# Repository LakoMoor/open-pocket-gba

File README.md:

# Open Pocket GBA

Experimental native FPGA Game Boy Advance work for the **Sipeed Tang Nano 20K (GW2AR-18)**,
based on [Open Pocket GBC](https://github.com/LakoMoor/open-pocket-gbc).
The original project history, GBC target and infrastructure are preserved.

**This is not a complete GBA implementation.** The current target executes an
original ARM/Thumb diagnostic in hardware RTL, uses SDRAM for GBA RAM/VRAM,
implements timers, ordinary four-channel DMA, keypad and LCD status/IRQ, and drives 240x160 RGB555 at 3x through the
existing 720x480 HDMI pipeline. CPU IRQ/SWI return, memory handshakes and complete
output frames have been checked in Verilator. Native CPU performance, a compatible
BIOS, full PPU, FIFO/capture DMA, audio, cartridge saves and the GBA menu are still missing.

This image is a simulated HDMI RGB capture, not a physical board demonstration.
See [confirmed progress and build results](docs/gba-progress.md),
[architecture audit](docs/gba-architecture.md), [memory/bandwidth budget](docs/gba-memory-budget.md)
and [compatibility limits](docs/gba-compatibility.md).

## Build and test

Only open-source tools: Yosys + slang, nextpnr-himbaechel, Apicula/gowin_pack,
Verilator and openFPGALoader. No mandatory Gowin EDA dependency.

```sh
python fw/gba/make_diagnostic.py
bash sim/gba/run.sh
bash sim/gba/board.sh
./build.sh gba_top
```

Override `TOOLS` to point to OSS CAD Suite; the existing Windows default is
`/e/tools/oss-cad-suite`. GBA build artifacts and timing logs go into
`build/gba_top/`. GBA timing failures prevent packing a bitstream.

The original Game Boy / Game Boy Color target remains separate:

```sh
./build.sh gbc_top
```

Its features, menu, firmware, wiring and flash instructions are documented in
[the preserved GBC README](README.gbc.md). `flash.sh` continues to select GBC;
it does not implicitly install GBA or change the existing firmware/save layout.

## Source and licensing

The console runs as FPGA logic, not software emulation on a RISC-V CPU or PC.
Only the CPU/Thumb decoder is imported from GBATang; the integration, memory
system, timer/IRQ module and diagnostic are separate work. Attribution and full
license texts are in [licenses](licenses/gba-provenance.md) and [LICENSE](LICENSE).
No proprietary BIOS or commercial ROM is included. The diagnostic's original
source and explicit instruction encodings are in `fw/gba/make_diagnostic.py`.

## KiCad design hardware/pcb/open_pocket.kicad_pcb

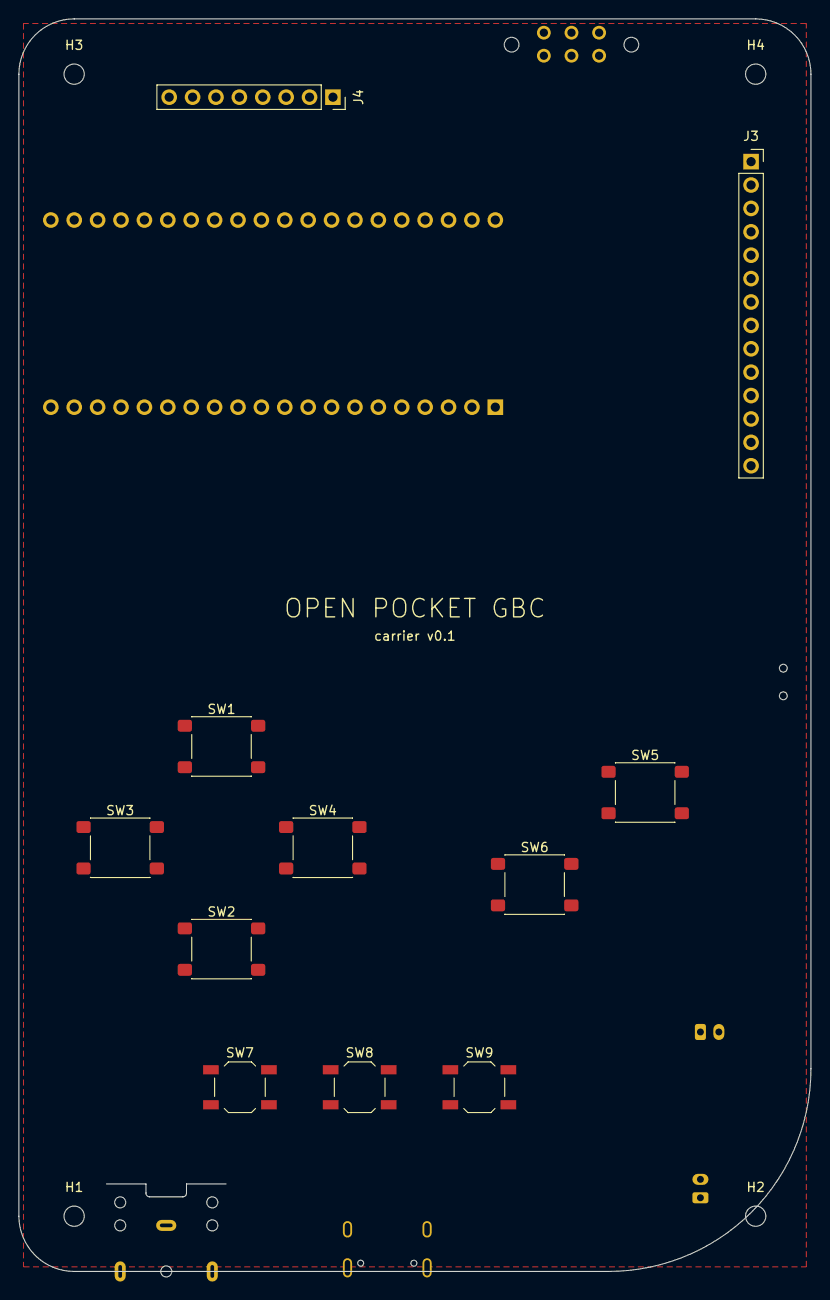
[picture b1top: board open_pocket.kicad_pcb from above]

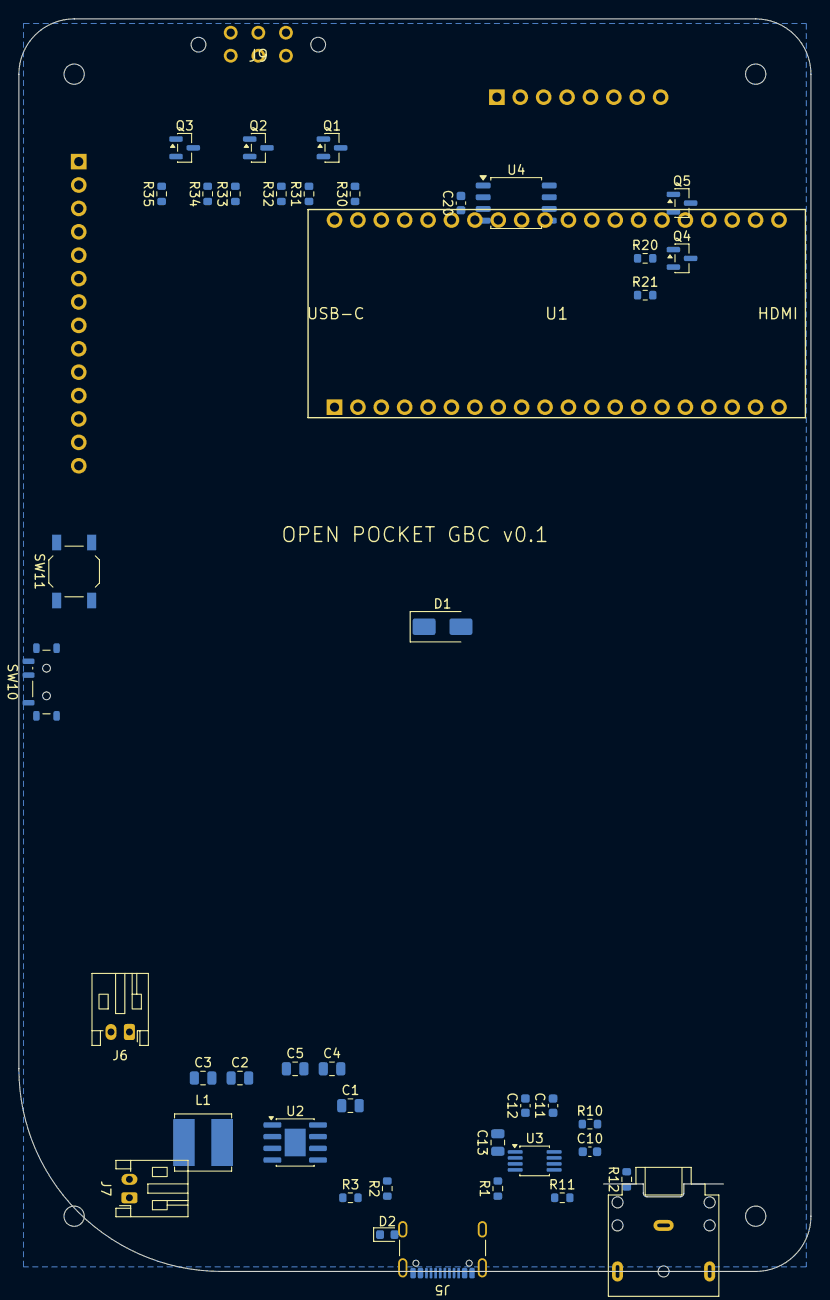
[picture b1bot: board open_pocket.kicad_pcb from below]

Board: 2 copper layers, 86.0 x 136.0 mm, 58 parts (43 on the bottom side), 48 nets, no tracks yet.

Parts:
C1, C2, C3, C13: 10uF; C_0805_2012Metric
C4, C5: 22uF; C_0805_2012Metric
C10: 10nF; C_0603_1608Metric
C11, C12: 1uF; C_0603_1608Metric
C20: 100nF; C_0603_1608Metric
D1: SS34; D_SMA
D2: LED charge; LED_0603_1608Metric
H1, H2, H3, H4: M2; MountingHole_2.2mm_M2
J3: LCD 2.4in ILI9341; PinSocket_1x14_P2.54mm_Vertical
J4: LCD 1.44in ST7735 (alt.); PinSocket_1x08_P2.54mm_Vertical
J5: USB-C (charge); USB_C_Receptacle_GCT_USB4105-xx-A_16P_TopMnt_Horizontal
J6: LiPo 3.7 V; JST_PH_S2B-PH-K_1x02_P2.00mm_Horizontal
J7: Speaker 8R 1W; JST_PH_S2B-PH-K_1x02_P2.00mm_Horizontal
J8: 3.5 mm; Jack_3.5mm_CUI_SJ1-3523N_Horizontal
J9: Link port; GB_Link_Port
L1: 1uH 4A; L_Bourns_SRN6045TA
Q1, Q2, Q3, Q4: BSS138; SOT-23
Q5: AO3401; SOT-23
R1, R2: 5.1k; R_0603_1608Metric
R3, R10: 1k; R_0603_1608Metric
R11, R21: 100k; R_0603_1608Metric
R12: 100R; R_0603_1608Metric
R20, R30, R31, R32, R33, R34, R35: 10k; R_0603_1608Metric
SW1: Up; SW_SPST_PTS645Sx43SMTR92
SW2: Down; SW_SPST_PTS645Sx43SMTR92
SW3: Left; SW_SPST_PTS645Sx43SMTR92
SW4: Right; SW_SPST_PTS645Sx43SMTR92
SW5: A; SW_SPST_PTS645Sx43SMTR92
SW6: B; SW_SPST_PTS645Sx43SMTR92
SW7: Select; SW_SPST_TL3342
SW8: Start; SW_SPST_TL3342
SW9: Menu; SW_SPST_TL3342
SW10: Power; SW_SPDT_Shouhan_MSK12C02
SW11: Wake / boost; SW_SPST_TL3342
U1: Tang Nano 20K; TangNano20K_Socket
U2: IP5306; SOIC-8-1EP_3.9x4.9mm_P1.27mm_EP2.29x3mm
U3: PAM8302A; MSOP-8_3x3mm_P0.65mm
U4: W25Q128JV; SOIC-8_5.3x5.3mm_P1.27mm

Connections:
+3V3: C20.1, J4.1, Q1.1, Q2.1, Q3.1, Q5.2, R20.2, R30.2, R32.2, R34.2, U1.19, U1.25, U4.3, U4.7, U4.8
AMP_EN: R11.1, U1.3, U3.1
AMP_INN: C12.1, U3.4
AMP_INP: C11.2, U3.3
AUDIO: C10.1, C11.1, R10.2, R12.1
AUDIO_PDM: R10.1, U1.38
BL_GATE: Q4.3, Q5.1, R20.1
BL_SW: J3.8, J4.8, Q5.3
CART_CLK: U1.31, U4.6
CART_CS: U1.32, U4.1
CART_DI: U1.30, U4.5
CART_DO: U1.29, U4.2
CC1: J5.A5, R1.1
CC2: J5.B5, R2.1
GND: C1.2, C2.2, C3.2, C4.2, C5.2, C10.2, C12.2, C13.2, C20.2, D2.1, J3.2, J4.2, J5.A1, J5.A12, J5.B1, J5.B12, J5.SH, J6.2, J8.S, J9.6, Q4.2, R1.2, R2.2, R11.2, R21.2, SW1.2, SW2.2, SW3.2, SW4.2, SW5.2, SW6.2, SW7.2, SW8.2, SW9.2, SW10.SH, SW11.2, U1.20, U1.26, U1.39, U2.9, U3.7, U4.4
HP_OUT: J8.R, J8.T, R12.2
IP_KEY: SW11.1, U2.5
IP_LED1: R3.1, U2.2
IP_SW: L1.1, U2.7
IP_VOUT: C4.1, C5.1, SW10.1, U2.8
KEY_A: SW5.1, U1.12
KEY_B: SW6.1, U1.13
KEY_DOWN: SW2.1, U1.11
KEY_LEFT: SW3.1, U1.8
KEY_MENU: SW9.1, U1.33
KEY_RIGHT: SW4.1, U1.9
KEY_SELECT: SW7.1, U1.14
KEY_START: SW8.1, U1.5
KEY_UP: SW1.1, U1.10
LCD_BL: Q4.1, R21.1, U1.21
LCD_CS: J3.3, J4.7, U1.22
LCD_DC: J3.5, J4.6, U1.24
LCD_MOSI: J3.6, J4.4, U1.2
LCD_RES: J3.4, J4.5, U1.23
LCD_SCK: J3.7, J4.3, U1.1
LED_CHG: D2.2, R3.2
LINK_SC_3V: Q3.2, R34.1, U1.35
LINK_SC_5V: J9.5, Q3.3, R35.1
LINK_SI_3V: Q2.2, R32.1, U1.36
LINK_SI_5V: J9.3, Q2.3, R33.1
LINK_SO_3V: Q1.2, R30.1, U1.34
LINK_SO_5V: J9.2, Q1.3, R31.1
SPK_N: J7.2, U3.8
SPK_P: J7.1, U3.5
SYS_5V: C13.1, D1.2, J3.1, J9.1, R31.2, R33.2, R35.2, SW10.2, U3.6
TANG_5V: D1.1, U1.40
VBAT: C2.1, C3.1, J6.1, L1.2, U2.6
VBUS: C1.1, J5.A4, J5.A9, J5.B4, J5.B9, U2.1

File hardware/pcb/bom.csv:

Ref,Value,Footprint,Part,Side
C1,10uF,Capacitor_SMD:C_0805_2012Metric,,back
C2,10uF,Capacitor_SMD:C_0805_2012Metric,,back
C3,10uF,Capacitor_SMD:C_0805_2012Metric,,back
C4,22uF,Capacitor_SMD:C_0805_2012Metric,,back
C5,22uF,Capacitor_SMD:C_0805_2012Metric,,back
C10,10nF,Capacitor_SMD:C_0603_1608Metric,,back
C11,1uF,Capacitor_SMD:C_0603_1608Metric,,back
C12,1uF,Capacitor_SMD:C_0603_1608Metric,,back
C13,10uF,Capacitor_SMD:C_0805_2012Metric,,back
C20,100nF,Capacitor_SMD:C_0603_1608Metric,,back
D1,SS34,Diode_SMD:D_SMA,,back
D2,LED charge,LED_SMD:LED_0603_1608Metric,,back
H1,M2,MountingHole:MountingHole_2.2mm_M2,,front
H2,M2,MountingHole:MountingHole_2.2mm_M2,,front
H3,M2,MountingHole:MountingHole_2.2mm_M2,,front
H4,M2,MountingHole:MountingHole_2.2mm_M2,,front
J3,LCD 2.4in ILI9341,Connector_PinSocket_2.54mm:PinSocket_1x14_P2.54mm_Vertical,"2.4"" SPI TFT 240x320 module",front
J4,LCD 1.44in ST7735 (alt.),Connector_PinSocket_2.54mm:PinSocket_1x08_P2.54mm_Vertical,"1.44"" SPI TFT 128x128 module",front
J5,USB-C (charge),Connector_USB:USB_C_Receptacle_GCT_USB4105-xx-A_16P_TopMnt_Horizontal,GCT USB4105-GF-A,back
J6,LiPo 3.7 V,Connector_JST:JST_PH_S2B-PH-K_1x02_P2.00mm_Horizontal,603450 1200 mAh with PH2.0 lead,back
J7,Speaker 8R 1W,Connector_JST:JST_PH_S2B-PH-K_1x02_P2.00mm_Horizontal,20 mm 8 ohm speaker,back
J8,3.5 mm,Connector_Audio:Jack_3.5mm_CUI_SJ1-3523N_Horizontal,CUI SJ1-3523N,back
J9,Link port,custom:J9,Game Boy Color link port socket,back
L1,1uH 4A,Inductor_SMD:L_Bourns_SRN6045TA,,back
Q1,BSS138,Package_TO_SOT_SMD:SOT-23,,back
Q2,BSS138,Package_TO_SOT_SMD:SOT-23,,back
Q3,BSS138,Package_TO_SOT_SMD:SOT-23,,back
Q4,BSS138,Package_TO_SOT_SMD:SOT-23,,back
Q5,AO3401,Package_TO_SOT_SMD:SOT-23,,back
R1,5.1k,Resistor_SMD:R_0603_1608Metric,,back
R2,5.1k,Resistor_SMD:R_0603_1608Metric,,back
R3,1k,Resistor_SMD:R_0603_1608Metric,,back
R10,1k,Resistor_SMD:R_0603_1608Metric,,back
R11,100k,Resistor_SMD:R_0603_1608Metric,,back
R12,100R,Resistor_SMD:R_0603_1608Metric,,back
R20,10k,Resistor_SMD:R_0603_1608Metric,,back
R21,100k,Resistor_SMD:R_0603_1608Metric,,back
R30,10k,Resistor_SMD:R_0603_1608Metric,,back
R31,10k,Resistor_SMD:R_0603_1608Metric,,back
R32,10k,Resistor_SMD:R_0603_1608Metric,,back
R33,10k,Resistor_SMD:R_0603_1608Metric,,back
R34,10k,Resistor_SMD:R_0603_1608Metric,,back
R35,10k,Resistor_SMD:R_0603_1608Metric,,back
SW1,Up,Button_Switch_SMD:SW_SPST_PTS645Sx43SMTR92,C&K PTS645SK43SMTR92,front
SW2,Down,Button_Switch_SMD:SW_SPST_PTS645Sx43SMTR92,C&K PTS645SK43SMTR92,front
SW3,Left,Button_Switch_SMD:SW_SPST_PTS645Sx43SMTR92,C&K PTS645SK43SMTR92,front
SW4,Right,Button_Switch_SMD:SW_SPST_PTS645Sx43SMTR92,C&K PTS645SK43SMTR92,front
SW5,A,Button_Switch_SMD:SW_SPST_PTS645Sx43SMTR92,C&K PTS645SK43SMTR92,front
SW6,B,Button_Switch_SMD:SW_SPST_PTS645Sx43SMTR92,C&K PTS645SK43SMTR92,front
SW7,Select,Button_Switch_SMD:SW_SPST_TL3342,TE TL3342,front
SW8,Start,Button_Switch_SMD:SW_SPST_TL3342,TE TL3342,front
SW9,Menu,Button_Switch_SMD:SW_SPST_TL3342,TE TL3342,front
SW10,Power,Button_Switch_SMD:SW_SPDT_Shouhan_MSK12C02,Shouhan MSK12C02,back
SW11,Wake / boost,Button_Switch_SMD:SW_SPST_TL3342,TE TL3342,back
U1,Tang Nano 20K,custom:U1,"2x PinSocket 1x20 2.54 mm, low profile",back
U2,IP5306,Package_SO:SOIC-8-1EP_3.9x4.9mm_P1.27mm_EP2.29x3mm,Injoinic IP5306,back
U3,PAM8302A,Package_SO:MSOP-8_3x3mm_P0.65mm,Diodes PAM8302AAYCR,back
U4,W25Q128JV,Package_SO:SOIC-8_5.3x5.3mm_P1.27mm,Winbond W25Q128JVSIQ,back

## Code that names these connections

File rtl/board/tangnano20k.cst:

// Sipeed Tang Nano 20K (GW2AR-LV18QN88C8/I7)

IO_LOC  "sys_clk" 4;
IO_PORT "sys_clk" IO_TYPE=LVCMOS33 PULL_MODE=NONE;

// Buttons (active high)
IO_LOC  "s1" 88;
IO_PORT "s1" IO_TYPE=LVCMOS33 PULL_MODE=DOWN;
IO_LOC  "s2" 87;
IO_PORT "s2" IO_TYPE=LVCMOS33 PULL_MODE=DOWN;

// LEDs (active low). LEDs 2..5 share pins 17..20 with the DualShock adapter.
IO_LOC  "led[0]" 15;
IO_PORT "led[0]" IO_TYPE=LVCMOS33 PULL_MODE=NONE DRIVE=8;
IO_LOC  "led[1]" 16;
IO_PORT "led[1]" IO_TYPE=LVCMOS33 PULL_MODE=NONE DRIVE=8;

// USB-C UART (BL616)
IO_LOC  "uart_tx" 69;
IO_PORT "uart_tx" IO_TYPE=LVCMOS33 PULL_MODE=UP;
IO_LOC  "uart_rx" 70;
IO_PORT "uart_rx" IO_TYPE=LVCMOS33 PULL_MODE=UP;

// HDMI
IO_LOC  "tmds_clk_p" 33;
IO_PORT "tmds_clk_p" IO_TYPE=LVDS25 PULL_MODE=NONE;
IO_LOC  "tmds_clk_n" 34;
IO_PORT "tmds_clk_n" IO_TYPE=LVDS25 PULL_MODE=NONE;
IO_LOC  "tmds_d_p[0]" 35;
IO_PORT "tmds_d_p[0]" IO_TYPE=LVDS25 PULL_MODE=NONE;
IO_LOC  "tmds_d_n[0]" 36;
IO_PORT "tmds_d_n[0]" IO_TYPE=LVDS25 PULL_MODE=NONE;
IO_LOC  "tmds_d_p[1]" 37;
IO_PORT "tmds_d_p[1]" IO_TYPE=LVDS25 PULL_MODE=NONE;
IO_LOC  "tmds_d_n[1]" 38;
IO_PORT "tmds_d_n[1]" IO_TYPE=LVDS25 PULL_MODE=NONE;
IO_LOC  "tmds_d_p[2]" 39;
IO_PORT "tmds_d_p[2]" IO_TYPE=LVDS25 PULL_MODE=NONE;
IO_LOC  "tmds_d_n[2]" 40;
IO_PORT "tmds_d_n[2]" IO_TYPE=LVDS25 PULL_MODE=NONE;

// DualShock 2 adapter (Sipeed retro kit), port 1
IO_LOC  "ds_clk" 17;
IO_PORT "ds_clk" IO_TYPE=LVCMOS33 PULL_MODE=NONE DRIVE=8;
IO_LOC  "ds_cs" 18;
IO_PORT "ds_cs" IO_TYPE=LVCMOS33 PULL_MODE=NONE DRIVE=8;
IO_LOC  "ds_miso" 19;
IO_PORT "ds_miso" IO_TYPE=LVCMOS33 PULL_MODE=UP;
IO_LOC  "ds_mosi" 20;
IO_PORT "ds_mosi" IO_TYPE=LVCMOS33 PULL_MODE=NONE DRIVE=8;

// GPIO buttons (to GND, internal pull-ups) on the header
// key_n: 0 up, 1 down, 2 left, 3 right, 4 A, 5 B, 6 select, 7 start
IO_LOC  "key_n[0]" 25;
IO_LOC  "key_n[1]" 26;
IO_LOC  "key_n[2]" 27;
IO_LOC  "key_n[3]" 28;
IO_LOC  "key_n[4]" 29;
IO_LOC  "key_n[5]" 30;
IO_LOC  "key_n[6]" 31;
IO_LOC  "key_n[7]" 77;
IO_PORT "key_n[0]" IO_TYPE=LVCMOS33 PULL_MODE=UP;
IO_PORT "key_n[1]" IO_TYPE=LVCMOS33 PULL_MODE=UP;
IO_PORT "key_n[2]" IO_TYPE=LVCMOS33 PULL_MODE=UP;
IO_PORT "key_n[3]" IO_TYPE=LVCMOS33 PULL_MODE=UP;
IO_PORT "key_n[4]" IO_TYPE=LVCMOS33 PULL_MODE=UP;
IO_PORT "key_n[5]" IO_TYPE=LVCMOS33 PULL_MODE=UP;
IO_PORT "key_n[6]" IO_TYPE=LVCMOS33 PULL_MODE=UP;
IO_PORT "key_n[7]" IO_TYPE=LVCMOS33 PULL_MODE=UP;

// ST7735S 128x128 SPI LCD (module pins: SCL/SCK, SDA/MOSI, RES, DC/A0, CS, BL)
IO_LOC  "lcd_scl" 73;
IO_PORT "lcd_scl" IO_TYPE=LVCMOS33 PULL_MODE=NONE DRIVE=8;
IO_LOC  "lcd_sda" 74;
IO_PORT "lcd_sda" IO_TYPE=LVCMOS33 PULL_MODE=NONE DRIVE=8;
IO_LOC  "lcd_rst" 71;
IO_PORT "lcd_rst" IO_TYPE=LVCMOS33 PULL_MODE=NONE DRIVE=8;
IO_LOC  "lcd_dc" 72;
IO_PORT "lcd_dc" IO_TYPE=LVCMOS33 PULL_MODE=NONE DRIVE=8;
IO_LOC  "lcd_cs" 53;
IO_PORT "lcd_cs" IO_TYPE=LVCMOS33 PULL_MODE=NONE DRIVE=8;
IO_LOC  "lcd_bl" 52;
IO_PORT "lcd_bl" IO_TYPE=LVCMOS33 PULL_MODE=NONE DRIVE=8;

// On-board SPI flash (bitstream + ROM storage)
IO_LOC  "flash_cs_n" 60;
IO_PORT "flash_cs_n" IO_TYPE=LVCMOS33 PULL_MODE=UP;
IO_LOC  "flash_clk" 59;
IO_PORT "flash_clk" IO_TYPE=LVCMOS33 PULL_MODE=NONE;
IO_LOC  "flash_mosi" 61;
IO_PORT "flash_mosi" IO_TYPE=LVCMOS33 PULL_MODE=NONE;
IO_LOC  "flash_miso" 62;
IO_PORT "flash_miso" IO_TYPE=LVCMOS33 PULL_MODE=UP;

// TF card slot (SPI mode)
IO_LOC  "sd_clk" 83;
IO_PORT "sd_clk" IO_TYPE=LVCMOS33 PULL_MODE=NONE DRIVE=8;
IO_LOC  "sd_cmd" 82;
IO_PORT "sd_cmd" IO_TYPE=LVCMOS33 PULL_MODE=NONE DRIVE=8;
IO_LOC  "sd_dat0" 84;
IO_PORT "sd_dat0" IO_TYPE=LVCMOS33 PULL_MODE=UP;
IO_LOC  "sd_dat1" 85;
IO_PORT "sd_dat1" IO_TYPE=LVCMOS33 PULL_MODE=NONE DRIVE=4;
IO_LOC  "sd_dat2" 80;
IO_PORT "sd_dat2" IO_TYPE=LVCMOS33 PULL_MODE=NONE DRIVE=4;
IO_LOC  "sd_dat3" 81;
IO_PORT "sd_dat3" IO_TYPE=LVCMOS33 PULL_MODE=NONE DRIVE=8;
// WS2812 RGB LED
IO_LOC  "ws2812" 79;
IO_PORT "ws2812" IO_TYPE=LVCMOS33 PULL_MODE=NONE DRIVE=4;

// buzzer / speaker (sigma-delta audio)
IO_LOC  "spk_p" 76;
IO_PORT "spk_p" IO_TYPE=LVCMOS33 PULL_MODE=NONE DRIVE=8;
IO_LOC  "spk_n" 75;
IO_PORT "spk_n" IO_TYPE=LVCMOS33 PULL_MODE=NONE DRIVE=8;

// carrier: USB power present (VBUS divider), pulled down when nothing is connected
IO_LOC  "chg" 86;
IO_PORT "chg" IO_TYPE=LVCMOS33 PULL_MODE=DOWN;

// Menu button of the carrier board, to GND
IO_LOC  "key_menu_n" 54;
IO_PORT "key_menu_n" IO_TYPE=LVCMOS33 PULL_MODE=UP;

// Game Boy link port; the original is 5 V logic: use a level shifter (BSS138 / TXS0104)
IO_LOC  "link_sc" 41;
IO_PORT "link_sc" IO_TYPE=LVCMOS33 PULL_MODE=UP DRIVE=8;
IO_LOC  "link_si" 42;
IO_PORT "link_si" IO_TYPE=LVCMOS33 PULL_MODE=UP;
IO_LOC  "link_so" 56;
IO_PORT "link_so" IO_TYPE=LVCMOS33 PULL_MODE=NONE DRIVE=8;

// external W25Qxx flash ("cartridge"); WP and HOLD of the chip go to 3V3
IO_LOC  "cart_cs_n" 51;
IO_PORT "cart_cs_n" IO_TYPE=LVCMOS33 PULL_MODE=NONE DRIVE=8;
IO_LOC  "cart_clk" 48;
IO_PORT "cart_clk" IO_TYPE=LVCMOS33 PULL_MODE=NONE DRIVE=8;
IO_LOC  "cart_mosi" 55;
IO_PORT "cart_mosi" IO_TYPE=LVCMOS33 PULL_MODE=NONE DRIVE=8;
IO_LOC  "cart_miso" 49;
IO_PORT "cart_miso" IO_TYPE=LVCMOS33 PULL_MODE=UP;
